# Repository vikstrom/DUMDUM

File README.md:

DUMDUM
======

DUMDUM DrUm Machine

A place to upload and manage all files tied to DUMDUM...code,logs,schematics and pcb-layout...

Schematics and pcb made in Eagle

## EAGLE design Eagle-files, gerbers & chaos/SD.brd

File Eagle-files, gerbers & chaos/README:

The board-file for the mixer is gone.

The Button-board is on the "to do"

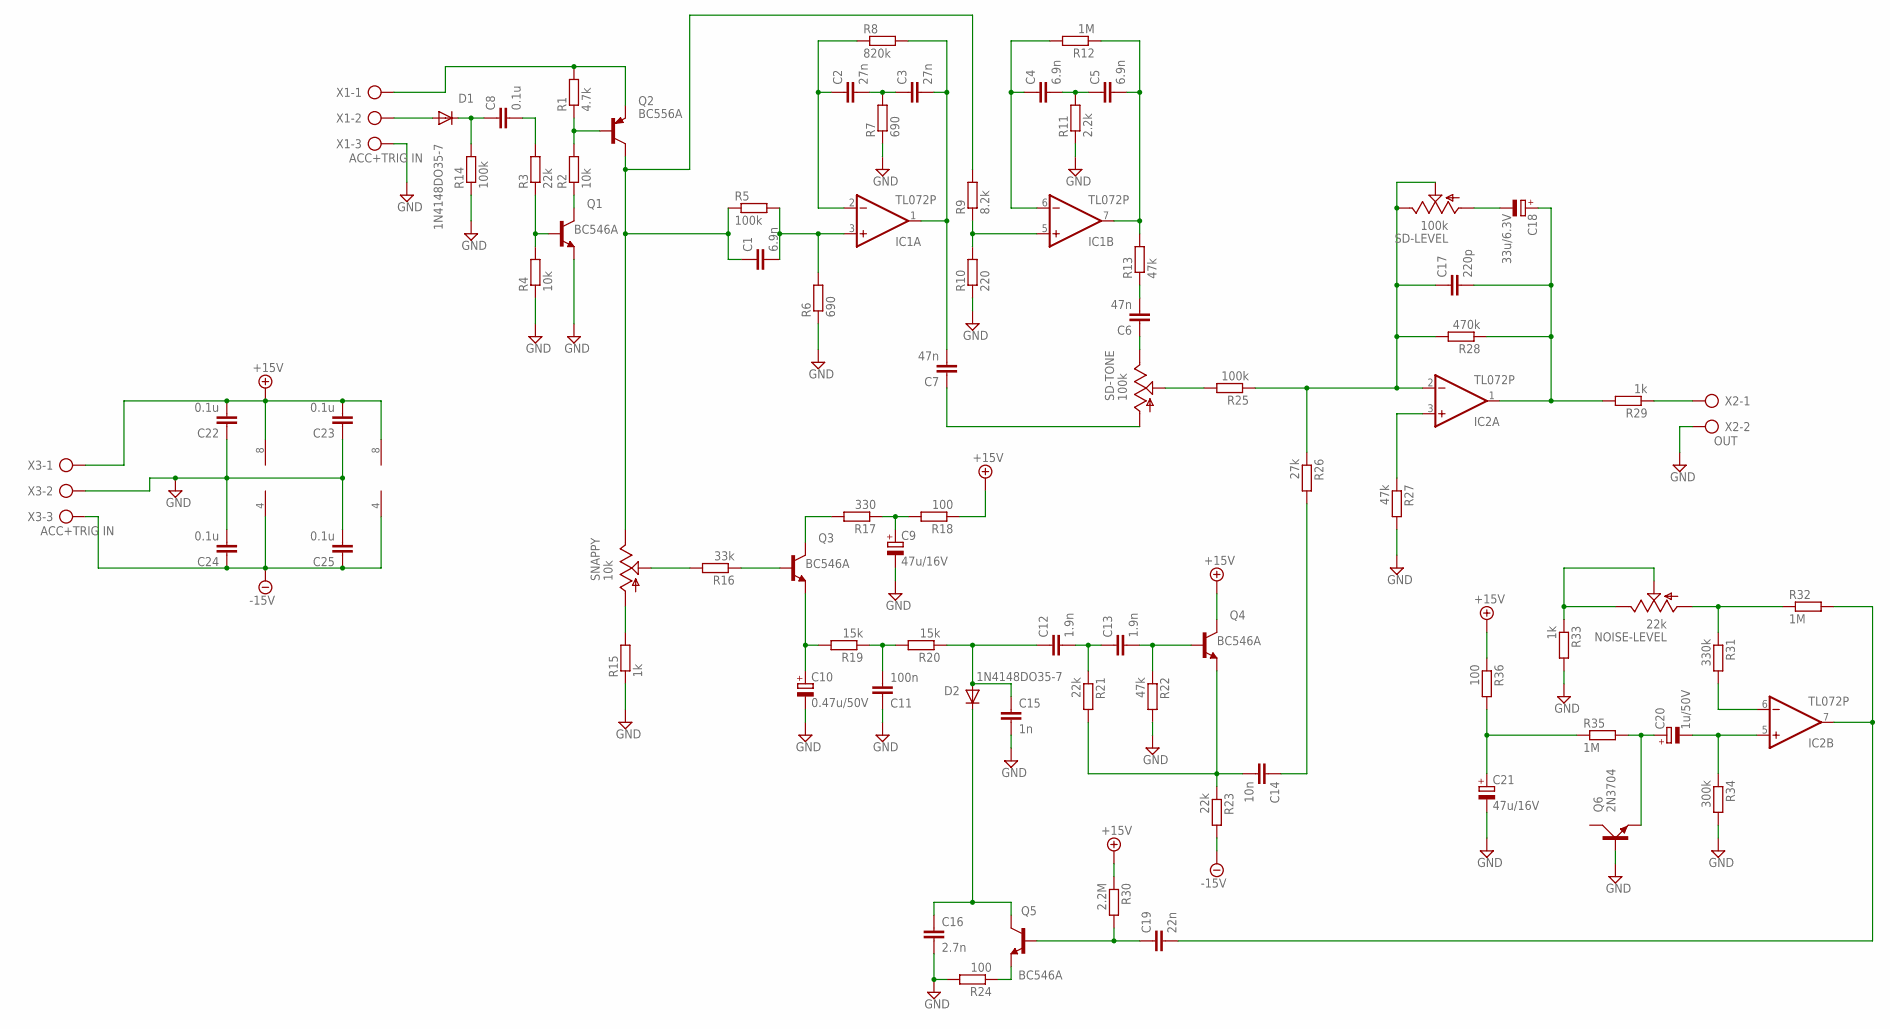
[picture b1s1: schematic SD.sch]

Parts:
C1, C4, C5: 6.9n; C075-042X103
C2, C3: 27n; C075-042X103
C6, C7: 47n; C075-042X103
C8, C22, C23, C24, C25: 0.1u; C075-042X103
C9, C21: 47u/16V; E2-5
C10: 0.47u/50V; E2-5
C11: 100n; C075-042X103
C12, C13: 1.9n; C075-042X103
C14: 10n; C075-042X103
C15: 1n; C075-042X103
C16: 2.7n; C075-042X103
C17: 220p; C075-042X103
C18: 33u/6.3V; E2-5
C19: 22n; C075-042X103
C20: 1u/50V; E2-5
D1, D2: 1N4148DO35-7; DO35-7
IC1, IC2: TL072P; DIL08
NOISE-LEVEL: 22k; ECP10P
Q1, Q3, Q4, Q5: BC546A; TO92-EBC
Q2: BC556A; TO92-EBC
Q6: 2N3704; TO92C
R1: 4.7k; 0207/10
R2, R4: 10k; 0207/10
R3, R21, R23: 22k; 0207/10
R5, R14, R25: 100k; 0207/10
R6, R7: 690; 0207/10
R8: 820k; 0207/10
R9: 8.2k; 0207/10
R10: 220; 0207/10
R11: 2.2k; 0207/10
R12, R32, R35: 1M; 0207/10
R13, R22, R27: 47k; 0207/10
R15, R29, R33: 1k; 0207/10
R16: 33k; 0207/10
R17: 330; 0207/10
R18, R24, R36: 100; 0207/10
R19, R20: 15k; 0207/10
R26: 27k; 0207/10
R28: 470k; 0207/10
R30: 2.2M; 0207/10
R31: 330k; 0207/10
R34: 300k; 0207/10
SD-LEVEL: 100k; ECP10P
SD-TONE: 100k; ECP10P
SNAPPY: 10k; ECP10P
X1, X3: ACC+TRIG IN; AK300/3
X2: OUT; AK300/2

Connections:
+15V: C22.2, C23.2, IC1.8 (V+), IC2.8 (V+), Q4.C, R18.1, R30.1, R36.1, X3.1
-15V: C24.1, C25.1, IC1.4 (V-), IC2.4 (V-), R23.2, X3.3
GND: C9.-, C10.-, C11.1, C15.2, C16.2, C21.-, C22.1, C23.1, C24.2, C25.2, Q1.E, Q6.B, R4.1, R6.1, R7.1, R10.1, R11.1, R14.1, R15.1, R22.2, R24.2, R27.2, R33.2, R34.2, X1.3, X2.2, X3.2
unnamed: Q2.E, R1.2, X1.1
unnamed: Q2.B, R1.1, R2.2
unnamed: Q1.C, R2.1
unnamed: C8.2, R3.2
unnamed: Q1.B, R3.1, R4.2
unnamed: C1.2, IC1.3 (+IN), R5.2, R6.2
unnamed: C1.1, Q2.C, R5.1, R9.2, SNAPPY.E
unnamed: C3.2, C7.2, IC1.1 (OUT), R8.2
unnamed: IC1.5 (+IN), R9.1, R10.2
unnamed: C2.1, IC1.2 (-IN), R8.1
unnamed: C2.2, C3.1, R7.2
unnamed: C7.1, SD-TONE.A
unnamed: C5.2, IC1.7 (OUT), R12.1, R13.2
unnamed: C4.1, IC1.6 (-IN), R12.2
unnamed: C4.2, C5.1, R11.2
unnamed: C6.1, SD-TONE.E
unnamed: C6.2, R13.1
unnamed: C8.1, D1.C, R14.2
unnamed: D1.A, X1.2
unnamed: R15.2, SNAPPY.A
unnamed: R16.2, SNAPPY.S
unnamed: Q3.B, R16.1
unnamed: Q3.C, R17.2
unnamed: C9.+, R17.1, R18.2
unnamed: C10.+, Q3.E, R19.2
unnamed: C11.2, R19.1, R20.2
unnamed: C13.2, Q4.B, R22.1
unnamed: C12.2, C13.1, R21.1
unnamed: C12.1, C15.1, D2.A, R20.1
unnamed: C14.2, Q4.E, R21.2, R23.1
unnamed: C16.1, D2.C, Q5.C
unnamed: R25.2, SD-TONE.S
unnamed: Q5.E, R24.1
unnamed: C14.1, R26.2
unnamed: C17.1, IC2.2 (-IN), R25.1, R26.1, R28.2, SD-LEVEL.E, SD-LEVEL.S
unnamed: IC2.3 (+IN), R27.1
unnamed: R29.1, X2.1
unnamed: C19.1, Q5.B, R30.2
unnamed: C18.-, SD-LEVEL.A
unnamed: C17.2, C18.+, IC2.1 (OUT), R28.1, R29.2
unnamed: C19.2, IC2.7 (OUT), R32.2
unnamed: NOISE-LEVEL.A, R31.1, R32.1
unnamed: IC2.6 (-IN), R31.2
unnamed: NOISE-LEVEL.E, NOISE-LEVEL.S, R33.1
unnamed: C20.-, IC2.5 (+IN), R34.1
unnamed: C20.+, Q6.E, R35.2
unnamed: C21.+, R35.1, R36.2

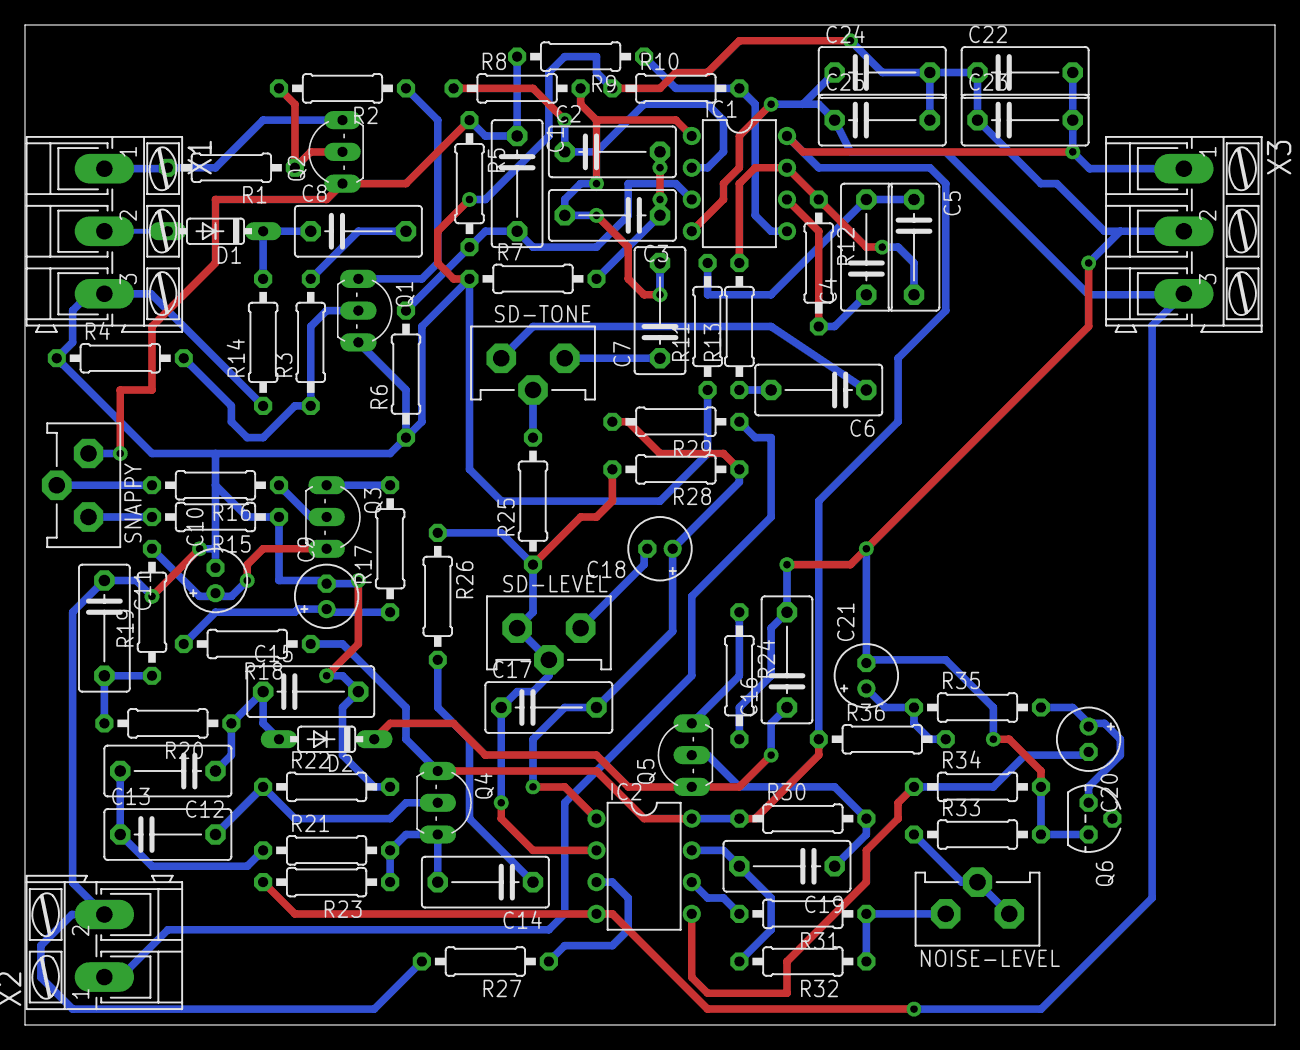
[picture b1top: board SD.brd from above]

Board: 2 copper layers, 100.0 x 80.0 mm, 78 parts (0 on the bottom side), 50 nets.

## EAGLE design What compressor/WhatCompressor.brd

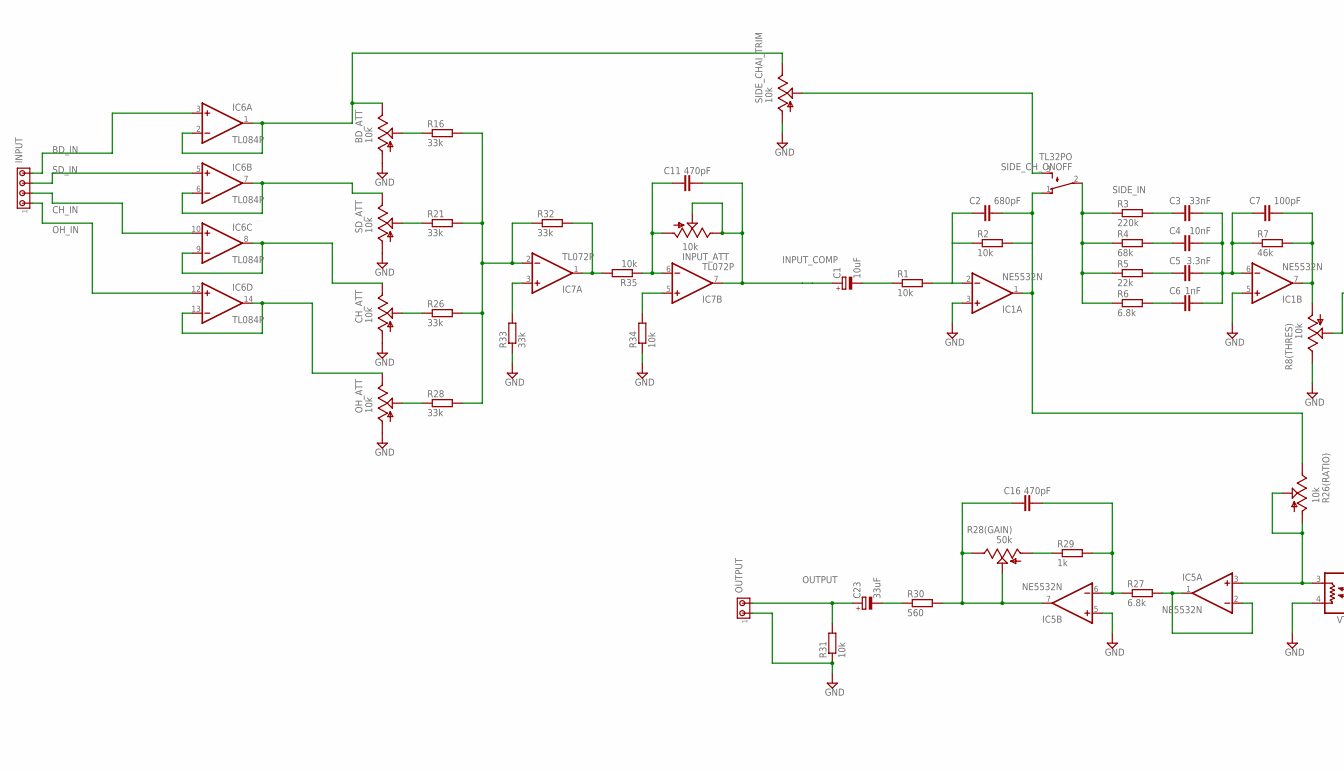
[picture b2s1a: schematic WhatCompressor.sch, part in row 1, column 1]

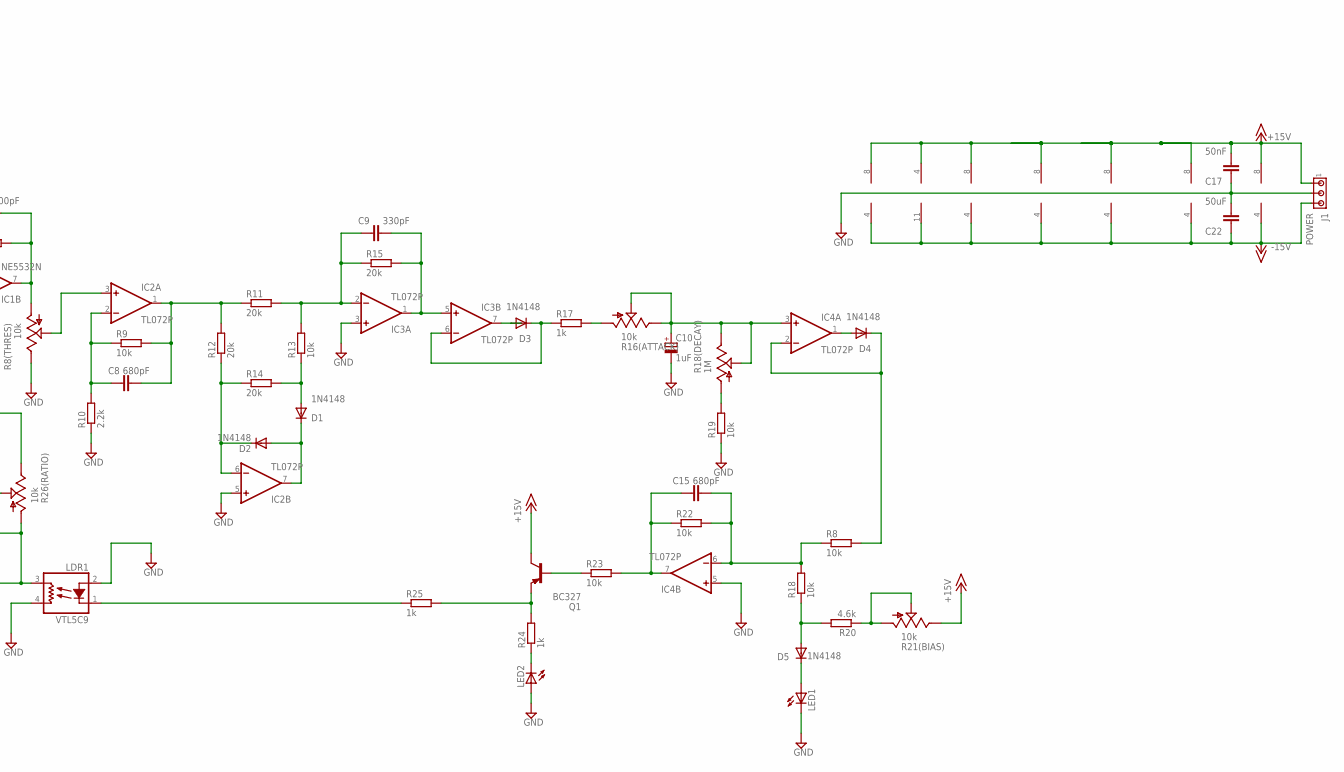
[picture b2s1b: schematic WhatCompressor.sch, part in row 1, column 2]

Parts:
BD_ATT: 10k; B64Y
C1: 10uF; E2,5-5; MPN 100PK10MEFC5X11
C2, C8, C15: 680pF; C050-024X044; MPN F681K33Y5RN6UK5R
C3: 33nF; C050-024X044; MPN SR201C333KAR
C4: 10nF; C050-024X044; MPN K103K15X7RF5TH5V
C5: 3.3nF; C050-024X044; MPN MCBU7332K6
C6: 1nF; C050-024X044; MPN K102K15X7RF5TH5V
C7: 100pF; C050-024X044; MPN F101K25Y5RP6UK5R
C9: 330pF; C050-024X044; MPN F331K29Y5RN6UK5R
C10: 1uF; E2,5-5; MPN ECEA1HKS010
C11, C16: 470pF; C050-024X044; MPN MCBU7332K6
C17: 50nF; C050-024X044; MPN K103K15X7RF5TH5V
C22: 50uF; C050-024X044; MPN K103K15X7RF5TH5V
C23: 33uF; E2,5-5; MPN 100PK10MEFC5X11
CH_ATT: 10k; B64Y
D1, D2, D3, D4, D5: 1N4148; DO35-7; MPN 1N4148
IC1: NE5532N; DIL08; MPN NE5532P
IC2, IC3, IC4: TL072P; DIL08; MPN TL072IP
IC5: NE5532N; DIL08
IC6: TL084P; DIL14
IC7: TL072P; DIL08
INPUT: MTA04-100; 10X04MTA
INPUT_ATT: 10k; B64Y
J1: POWER; 10X03MTA
LDR1: VTL5C9; VTL5C
LED1, LED2: LED5MM
OH_ATT: 10k; B64Y
OUTPUT: MTA02-100; 10X02MTA
Q1: BC327; TO92-EBC
R1, R2, R9, R13, R19, R31: 10k; 0204/7; MPN MCCFR0W4J0103A50
R3: 220k; 0204/7; MPN CFR16J220K
R4: 68k; 0204/7; MPN CFR16J68K
R5: 22k; 0204/7; MPN CFR16J22K
R6, R27: 6.8k; 0204/7; MPN MF25 6K8
R7: 46k; 0204/7; MPN CFR16J47K
R8, R18: 10k; 0204/7; MPN MCF 0.25W 1K
R8(THRES), R16(ATTACK), R21(BIAS), R26(RATIO): 10k; B64Y
R10: 2.2k; 0204/7; MPN MF25 2K2
R11, R12, R14, R15: 20k; 0204/7; MPN LR0204F20K
R16, R21, R26, R28, R32, R33: 33k; 0204/7; MPN CFR16J220K
R17: 1k; 0204/7; MPN MCF 0.25W 1K
R18(DECAY): 1M; B64Y
R20: 4.6k; 0204/7; MPN MCF 0.25W 1K
R22, R23: 10k; 0204/7; MPN LR0204F20K
R24, R25: 1k; 0204/7; MPN LR0204F20K
R28(GAIN): 50k; B64Y
R29: 1k; 0204/7; MPN MF25 6K8
R30: 560; 0204/7; MPN MCCFR0W4J0103A50
R34, R35: 10k; 0204/7; MPN CFR16J220K
SD_ATT: 10k; B64Y
SIDE_CHAI_TRIM: 10k; B64Y
SIDE_CH_ONOFF: TL32PO; TL3XPO

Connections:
+15V: C17.2, IC1.8 (V+), IC2.8 (V+), IC3.8 (V+), IC4.8 (V+), IC5.8 (V+), IC6.4 (V+), IC7.8 (V+), J1.1, Q1.C, R21(BIAS).E
-15V: C22.1, IC1.4 (V-), IC2.4 (V-), IC3.4 (V-), IC4.4 (V-), IC5.4 (V-), IC6.11 (V-), IC7.4 (V-), J1.3
BD_IN: IC6.3 (+IN), INPUT.4
CH_IN: IC6.10 (+IN), INPUT.2
GND: BD_ATT.A, C10.-, C17.1, C22.2, CH_ATT.A, IC1.3 (+IN), IC1.5 (+IN), IC2.5 (+IN), IC3.3 (+IN), IC4.5 (+IN), IC5.5 (+IN), J1.2, LDR1.2 (A), LDR1.4 (L2), LED1.K (C), LED2.A, OH_ATT.A, OUTPUT.1, R8(THRES).E, R10.1, R19.1, R31.1, R33.1, R34.1, SD_ATT.A, SIDE_CHAI_TRIM.A
INPUT_COMP: C1.+, C11.2, IC7.7 (OUT), INPUT_ATT.E, INPUT_ATT.S
unnamed: BD_ATT.E, IC6.1 (OUT), IC6.2 (-IN), SIDE_CHAI_TRIM.E
unnamed: C1.-, R1.1
unnamed: C2.1, IC1.2 (-IN), R1.2, R2.1
unnamed: IC6.6 (-IN), IC6.7 (OUT), SD_ATT.E
unnamed: C3.1, R3.2
unnamed: CH_ATT.E, IC6.8 (OUT), IC6.9 (-IN)
unnamed: C4.1, R4.2
unnamed: C5.1, R5.2
unnamed: C6.1, R6.2
unnamed: C3.2, C4.2, C5.2, C6.2, C7.1, IC1.6 (-IN), R7.1
unnamed: C7.2, IC1.7 (OUT), R7.2, R8(THRES).A
unnamed: C8.1, IC2.2 (-IN), R9.1, R10.2
unnamed: C8.2, IC2.1 (OUT), R9.2, R11.1, R12.2
unnamed: IC2.3 (+IN), R8(THRES).S
unnamed: C9.1, IC3.2 (-IN), R11.2, R13.2, R15.1
unnamed: D2.C, IC2.6 (-IN), R12.1, R14.1
unnamed: D1.A, R13.1, R14.2
unnamed: D1.C, D2.A, IC2.7 (OUT)
unnamed: C9.2, IC3.1 (OUT), IC3.5 (+IN), R15.2
unnamed: D3.C, IC3.6 (-IN), R17.1
unnamed: D3.A, IC3.7 (OUT)
unnamed: D5.A, R18.1, R20.2
unnamed: R16(ATTACK).A, R17.2
unnamed: C10.+, IC4.3 (+IN), R16(ATTACK).E, R16(ATTACK).S, R18(DECAY).E, R18(DECAY).S
unnamed: R18(DECAY).A, R19.2
unnamed: D4.C, IC4.2 (-IN), R8.2
unnamed: D4.A, IC4.1 (OUT)
unnamed: C15.2, IC4.6 (-IN), R8.1, R18.2, R22.2
unnamed: D5.C, LED1.A
unnamed: R20.1, R21(BIAS).A, R21(BIAS).S
unnamed: LED2.K (C), R24.1
unnamed: C15.1, IC4.7 (OUT), R22.1, R23.2
unnamed: Q1.E, R24.2, R25.2
unnamed: Q1.B, R23.1
unnamed: LDR1.1 (C), R25.1
unnamed: IC5.3 (+IN), LDR1.3 (L1), R26(RATIO).A, R26(RATIO).S
unnamed: IC5.1 (OUT), IC5.2 (-IN), R27.2
unnamed: C16.2, IC5.6 (-IN), R27.1, R29.2
unnamed: C23.-, R30.1
unnamed: R28(GAIN).A, R29.1
unnamed: C16.1, IC5.7 (OUT), R28(GAIN).E, R28(GAIN).S, R30.2
unnamed: SIDE_CHAI_TRIM.S, SIDE_CH_ONOFF.3 (S)
unnamed: IC6.13 (-IN), IC6.14 (OUT), OH_ATT.E
unnamed: BD_ATT.S, R16.1
unnamed: R21.1, SD_ATT.S
unnamed: CH_ATT.S, R26.1
unnamed: OH_ATT.S, R28.1
unnamed: IC7.2 (-IN), R16.2, R21.2, R26.2, R28.2, R32.1
unnamed: IC7.3 (+IN), R33.2
unnamed: IC7.1 (OUT), R32.2, R35.2
unnamed: C11.1, IC7.6 (-IN), INPUT_ATT.A, R35.1
unnamed: IC7.5 (+IN), R34.2
OH_IN: IC6.12 (+IN), INPUT.1
OUTPUT: C23.+, OUTPUT.2, R31.2
SD_IN: IC6.5 (+IN), INPUT.3
SIDE_IN: R3.1, R4.1, R5.1, R6.1, SIDE_CH_ONOFF.2
SIDE_OUT: C2.2, IC1.1 (OUT), R2.2, R26(RATIO).E, SIDE_CH_ONOFF.1 (O)

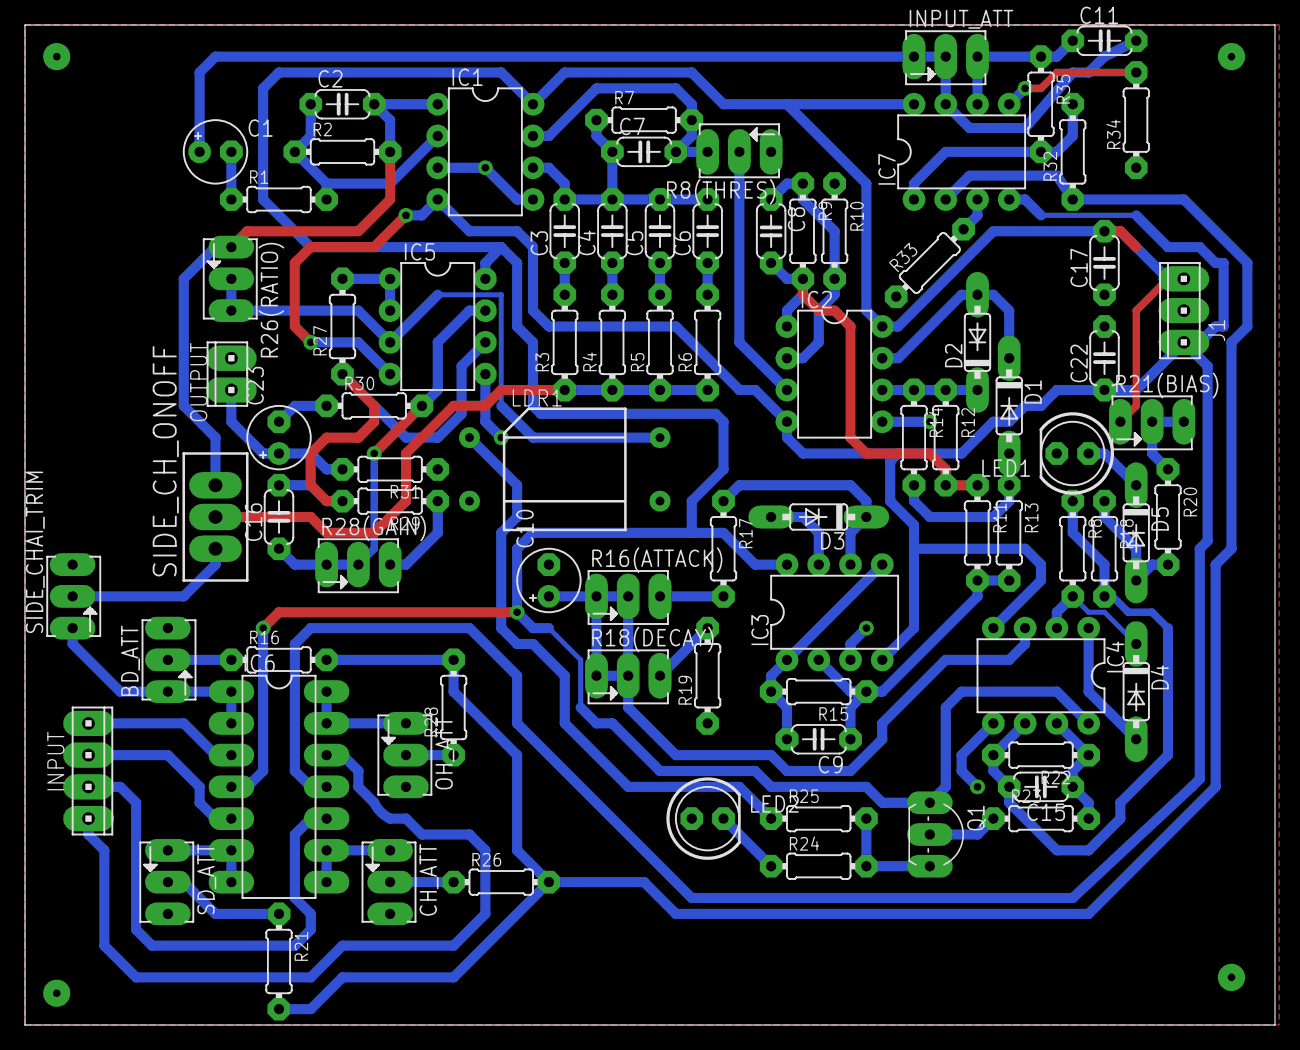
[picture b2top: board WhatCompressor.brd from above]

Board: 2 copper layers, 100.0 x 80.0 mm, 83 parts (0 on the bottom side), 63 nets.

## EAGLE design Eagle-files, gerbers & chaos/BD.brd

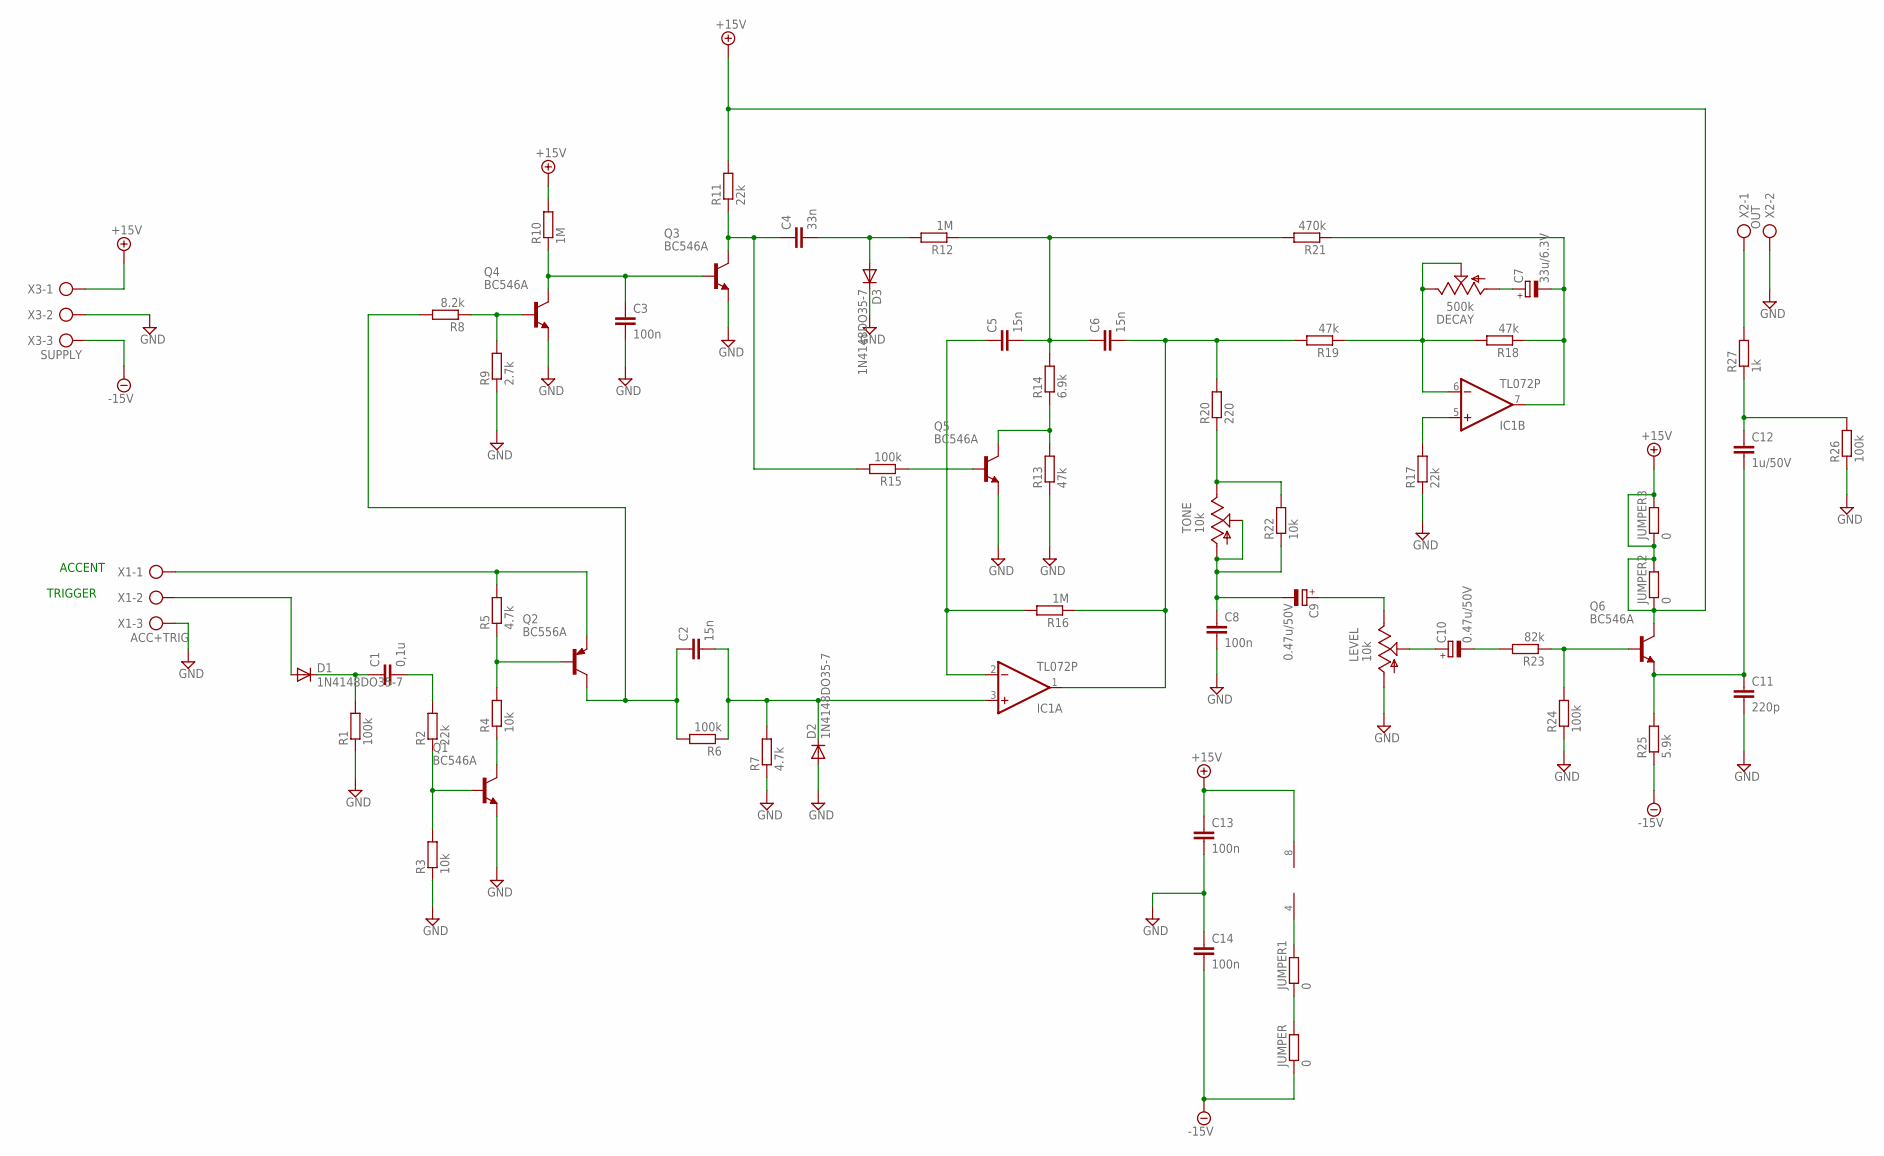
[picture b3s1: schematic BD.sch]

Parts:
C1: 0,1u; C075-042X103
C2, C5, C6: 15n; C075-042X103
C3, C8, C13, C14: 100n; C075-042X103
C4: 33n; C075-042X103
C7: 33u/6.3V; E2-5
C9, C10: 0.47u/50V; E2-5
C11: 220p; C075-042X103
C12: 1u/50V; C075-042X103
D1, D2, D3: 1N4148DO35-7; DO35-7
DECAY: 500k; CA9H
IC1: TL072P; DIL08
JUMPER, JUMPER1, JUMPER2, JUMPER3: 0; 0207/10
LEVEL: 10k; CA9H
Q1, Q3, Q4, Q5, Q6: BC546A; TO92-EBC
Q2: BC556A; TO92-EBC
R1, R6, R15, R24, R26: 100k; 0207/10
R2, R11, R17: 22k; 0207/10
R3, R4, R22: 10k; 0207/10
R5, R7: 4.7k; 0207/10
R8: 8.2k; 0207/10
R9: 2.7k; 0207/10
R10, R12, R16: 1M; 0207/10
R13, R18, R19: 47k; 0207/10
R14: 6.9k; 0207/10
R20: 220; 0207/10
R21: 470k; 0207/10
R23: 82k; 0207/10
R25: 5.9k; 0207/10
R27: 1k; 0207/10
TONE: 10k; CA9H
X1: ACC+TRIG; AK300/3
X2: OUT; AK300/2
X3: SUPPLY; AK300/3

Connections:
+15V: C13.1, IC1.8 (V+), JUMPER2.1, JUMPER2.2, JUMPER3.1, JUMPER3.2, Q6.C, R10.2, R11.2, X3.1
-15V: C14.2, JUMPER.1, R25.1, X3.3
GND: C3.2, C8.2, C11.2, C13.2, C14.1, D2.A, D3.C, LEVEL.A, Q1.E, Q3.E, Q4.E, Q5.E, R1.1, R3.1, R7.1, R9.1, R13.1, R17.1, R24.1, R26.1, X1.3, X2.2, X3.2
unnamed: Q2.E, R5.2, X1.1
unnamed: C1.1, D1.C, R1.2
unnamed: C1.2, R2.2
unnamed: Q1.B, R2.1, R3.2
unnamed: DECAY.E, DECAY.S, IC1.6 (-IN), R18.2, R19.1
unnamed: Q1.C, R4.1
unnamed: Q2.B, R4.2, R5.1
unnamed: D1.A, X1.2
unnamed: C2.1, Q2.C, R6.2, R8.2
unnamed: C2.2, D2.C, IC1.3 (+IN), R6.1, R7.2
unnamed: Q4.B, R8.1, R9.2
unnamed: C4.2, D3.A, R12.2
unnamed: C3.1, Q3.B, Q4.C, R10.1
unnamed: C4.1, Q3.C, R11.1, R15.2
unnamed: Q5.B, R15.1
unnamed: Q5.C, R13.2, R14.1
unnamed: IC1.5 (+IN), R17.2
unnamed: JUMPER.2, JUMPER1.1
unnamed: C5.1, IC1.2 (-IN), R16.2
unnamed: C6.2, IC1.1 (OUT), R16.1, R19.2, R20.2
unnamed: C7.-, IC1.7 (OUT), R18.1, R21.1
unnamed: C7.+, DECAY.A
unnamed: IC1.4 (V-), JUMPER1.2
unnamed: R20.1, R22.2, TONE.E
unnamed: C8.1, C9.-, R22.1, TONE.A, TONE.S
unnamed: C10.+, LEVEL.S
unnamed: C10.-, R23.2
unnamed: Q6.B, R23.1, R24.2
unnamed: C9.+, LEVEL.E
unnamed: C11.1, C12.2, Q6.E, R25.2
unnamed: C12.1, R26.2, R27.1
unnamed: R27.2, X2.1
unnamed: C5.2, C6.1, R12.1, R14.2, R21.2

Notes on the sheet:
ACCENT
TRIGGER

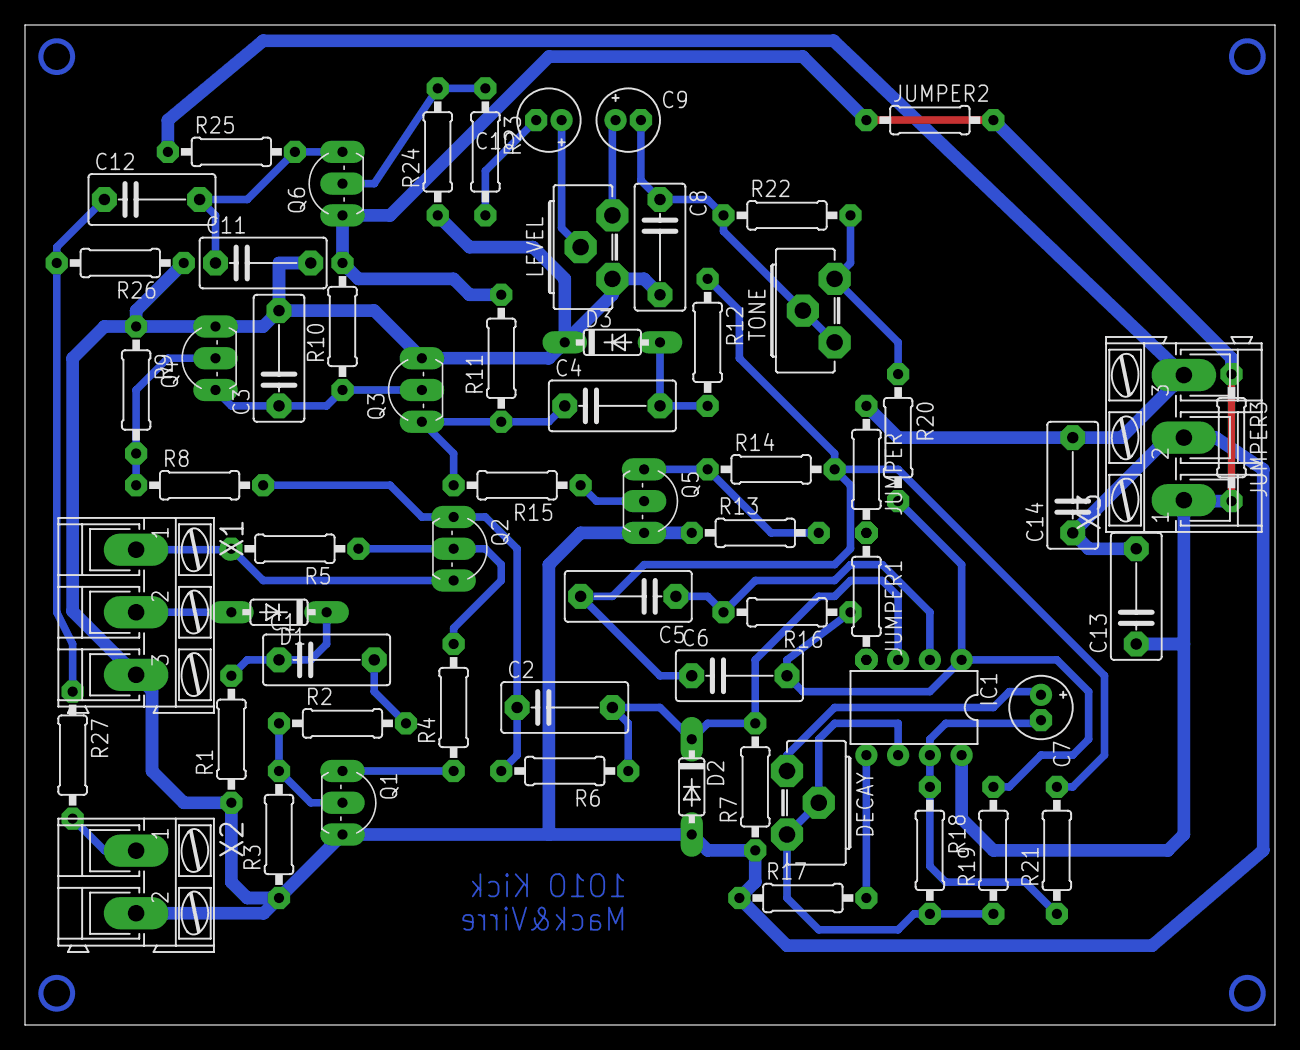
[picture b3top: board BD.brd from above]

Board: 2 copper layers, 100.0 x 80.0 mm, 61 parts (0 on the bottom side), 36 nets.

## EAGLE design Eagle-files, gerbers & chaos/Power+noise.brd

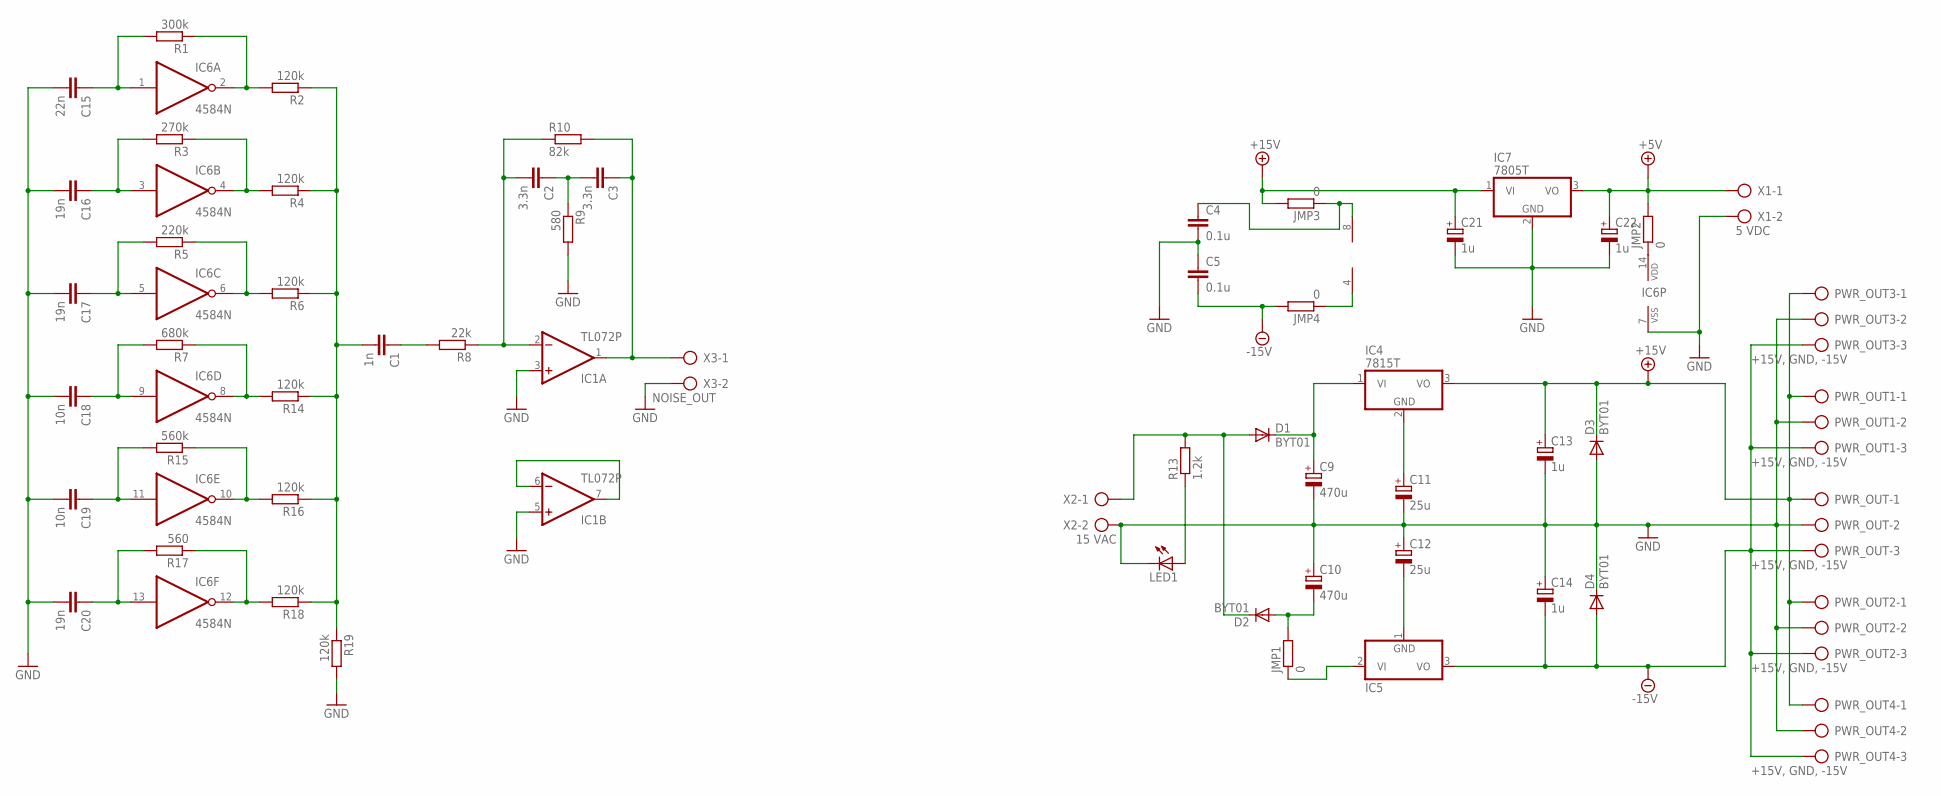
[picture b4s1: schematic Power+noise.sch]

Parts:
C1: 1n; C075-042X103
C2, C3: 3.3n; C075-042X103
C4, C5: 0.1u; C075-042X103
C9, C10: 470u; E5-6
C11, C12: 25u; E5-6
C13, C14, C21, C22: 1u; E5-6
C15: 22n; C075-042X103
C16, C17, C20: 19n; C075-042X103
C18, C19: 10n; C075-042X103
D1, D2, D3, D4: BYT01; F126-10
IC1: TL072P; DIL08
IC4: 7815T; TO220H
IC5: 7915T; TO220H
IC6: 4584N; DIL14
IC7: 7805T; TO220H
JMP1, JMP2, JMP4: 0; 0207/10
JMP3: 0; 0207/12
LED1: LED5MM
PWR_OUT, PWR_OUT1, PWR_OUT2, PWR_OUT3, PWR_OUT4: +15V, GND, -15V; AK300/3
R1: 300k; 0207/5V
R2, R4, R6, R14, R16, R18, R19: 120k; 0207/5V
R3: 270k; 0207/5V
R5: 220k; 0207/5V
R7: 680k; 0207/5V
R8: 22k; 0207/5V
R9: 580; 0207/5V
R10: 82k; 0207/5V
R13: 1.2k; 0207/5V
R15: 560k; 0207/5V
R17: 560; 0207/5V
X1: 5 VDC; AK300/2
X2: 15 VAC; AK300/2
X3: NOISE_OUT; AK300/2

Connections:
+5V: C22.+, IC7.3 (VO), JMP2.2, X1.1
+15V: C13.+, C21.+, D3.C, IC4.3 (VO), IC7.1 (VI), JMP3.2, PWR_OUT.1, PWR_OUT1.1, PWR_OUT2.1, PWR_OUT3.1, PWR_OUT4.1
-15V: C5.2, C14.-, D4.A, IC5.3 (VO), JMP4.2, PWR_OUT.3, PWR_OUT1.3, PWR_OUT2.3, PWR_OUT3.3, PWR_OUT4.3
GND: C4.2, C5.1, C9.-, C10.+, C11.-, C12.+, C13.-, C14.+, C15.2, C16.2, C17.2, C18.2, C19.2, C20.2, C21.-, C22.-, D3.A, D4.C, IC1.3 (+IN), IC1.5 (+IN), IC6.7 (VSS), IC7.2 (GND), LED1.K (C), PWR_OUT.2, PWR_OUT1.2, PWR_OUT2.2, PWR_OUT3.2, PWR_OUT4.2, R9.2, R19.2, X1.2, X2.2, X3.2
unnamed: C1.2, R2.1, R4.1, R6.1, R14.1, R16.1, R18.1, R19.1
unnamed: IC6.12 (O), R17.1, R18.2
unnamed: IC6.10 (O), R15.1, R16.2
unnamed: IC6.8 (O), R7.1, R14.2
unnamed: IC6.6 (O), R5.1, R6.2
unnamed: IC6.4 (O), R3.1, R4.2
unnamed: IC6.2 (O), R1.1, R2.2
unnamed: C20.1, IC6.13 (I), R17.2
unnamed: C19.1, IC6.11 (I), R15.2
unnamed: C10.-, D2.A, JMP1.2
unnamed: C1.1, R8.2
unnamed: C2.2, IC1.2 (-IN), R8.1, R10.1
unnamed: C3.1, IC1.1 (OUT), R10.2, X3.1
unnamed: C2.1, C3.2, R9.1
unnamed: C18.1, IC6.9 (I), R7.2
unnamed: C17.1, IC6.5 (I), R5.2
unnamed: C16.1, IC6.3 (I), R3.2
unnamed: C15.1, IC6.1 (I), R1.2
unnamed: D1.A, D2.C, R13.2, X2.1
unnamed: LED1.A, R13.1
unnamed: IC1.6 (-IN), IC1.7 (OUT)
unnamed: C9.+, D1.C, IC4.1 (VI)
unnamed: IC5.2 (VI), JMP1.1
unnamed: C11.+, IC4.2 (GND)
unnamed: IC6.14 (VDD), JMP2.1
unnamed: C12.-, IC5.1 (GND)
unnamed: IC1.4 (V-), JMP4.1
unnamed: C4.1, IC1.8 (V+), JMP3.1

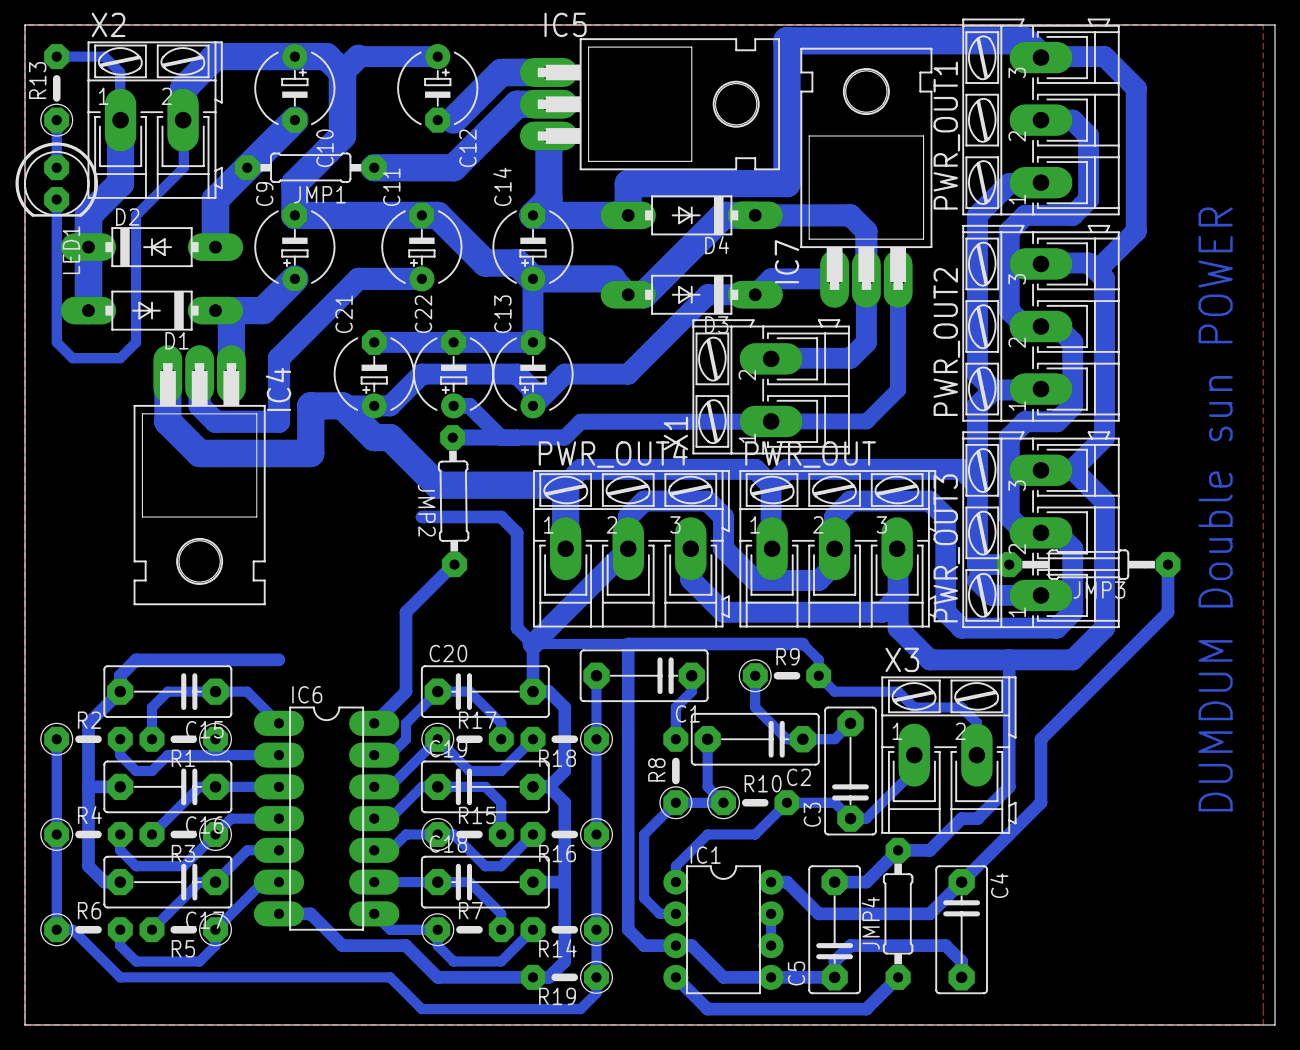
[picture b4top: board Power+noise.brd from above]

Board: 2 copper layers, 100.0 x 80.0 mm, 58 parts (0 on the bottom side), 32 nets.
